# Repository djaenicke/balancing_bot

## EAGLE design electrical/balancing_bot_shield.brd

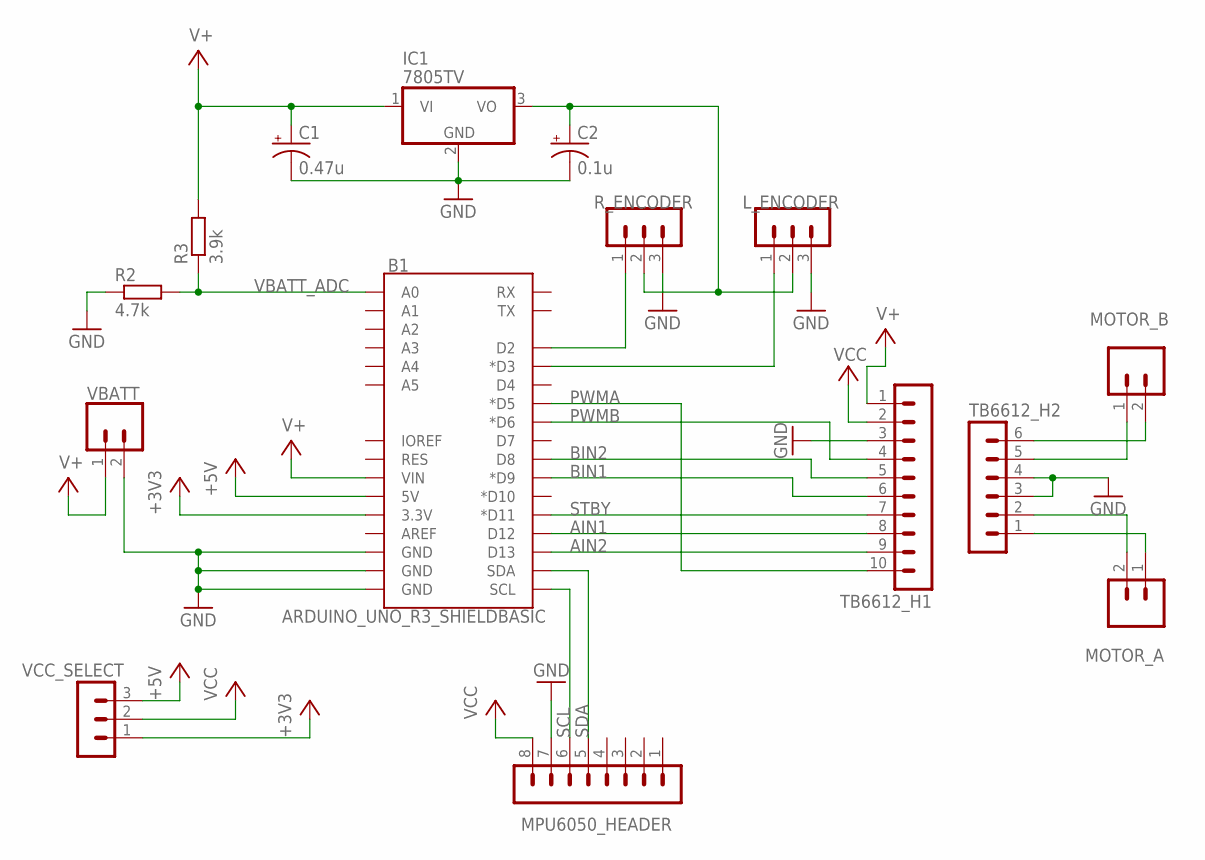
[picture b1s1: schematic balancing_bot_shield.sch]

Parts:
B1: ARDUINO_UNO_R3_SHIELDBASIC; UNO_R3_SHIELD
C1: 0.47u; E5-5
C2: 0.1u; E5-5
IC1: 7805TV; TO220V
L_ENCODER: MA03-1
MOTOR_A: CONN_025MM; SCREWTERMINAL-5MM-2
MOTOR_B: CONN_025MM; SCREWTERMINAL-5MM-2
MPU6050_HEADER: MA08-1
R2: 4.7k; 0207/10
R3: 3.9k; 0207/10
R_ENCODER: MA03-1
TB6612_H1: MA10-1
TB6612_H2: MA06-1
VBATT: CONN_025MM; SCREWTERMINAL-5MM-2
VCC_SELECT: MA03-1

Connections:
+3V3: B1.3.3V, VCC_SELECT.1
+5V: B1.5V, VCC_SELECT.3
AIN1: B1.D12, TB6612_H1.8
AIN2: B1.D13, TB6612_H1.9
BIN1: B1.D9 (*D9), TB6612_H1.6
BIN2: B1.D8, TB6612_H1.5
GND: B1.GND@0 (GND), B1.GND@1 (GND), B1.GND@2 (GND), C1.-, C2.-, IC1.2 (GND), L_ENCODER.3, MPU6050_HEADER.7, R2.1, R_ENCODER.3, TB6612_H1.3, TB6612_H2.3, TB6612_H2.4, VBATT.2
unnamed: B1.D2, R_ENCODER.1
unnamed: B1.D3 (*D3), L_ENCODER.1
unnamed: MOTOR_B.2, TB6612_H2.6
unnamed: MOTOR_B.1, TB6612_H2.5
unnamed: MOTOR_A.2, TB6612_H2.2
unnamed: MOTOR_A.1, TB6612_H2.1
unnamed: C2.+, IC1.3 (VO), L_ENCODER.2, R_ENCODER.2
PWMA: B1.D5 (*D5), TB6612_H1.10
PWMB: B1.D6 (*D6), TB6612_H1.4
SCL: B1.SCL, MPU6050_HEADER.6
SDA: B1.SDA, MPU6050_HEADER.5
STBY: B1.D11 (*D11), TB6612_H1.7
V+: B1.VIN, C1.+, IC1.1 (VI), R3.2, TB6612_H1.1, VBATT.1
VBATT_ADC: B1.A0, R2.2, R3.1
VCC: MPU6050_HEADER.8, TB6612_H1.2, VCC_SELECT.2

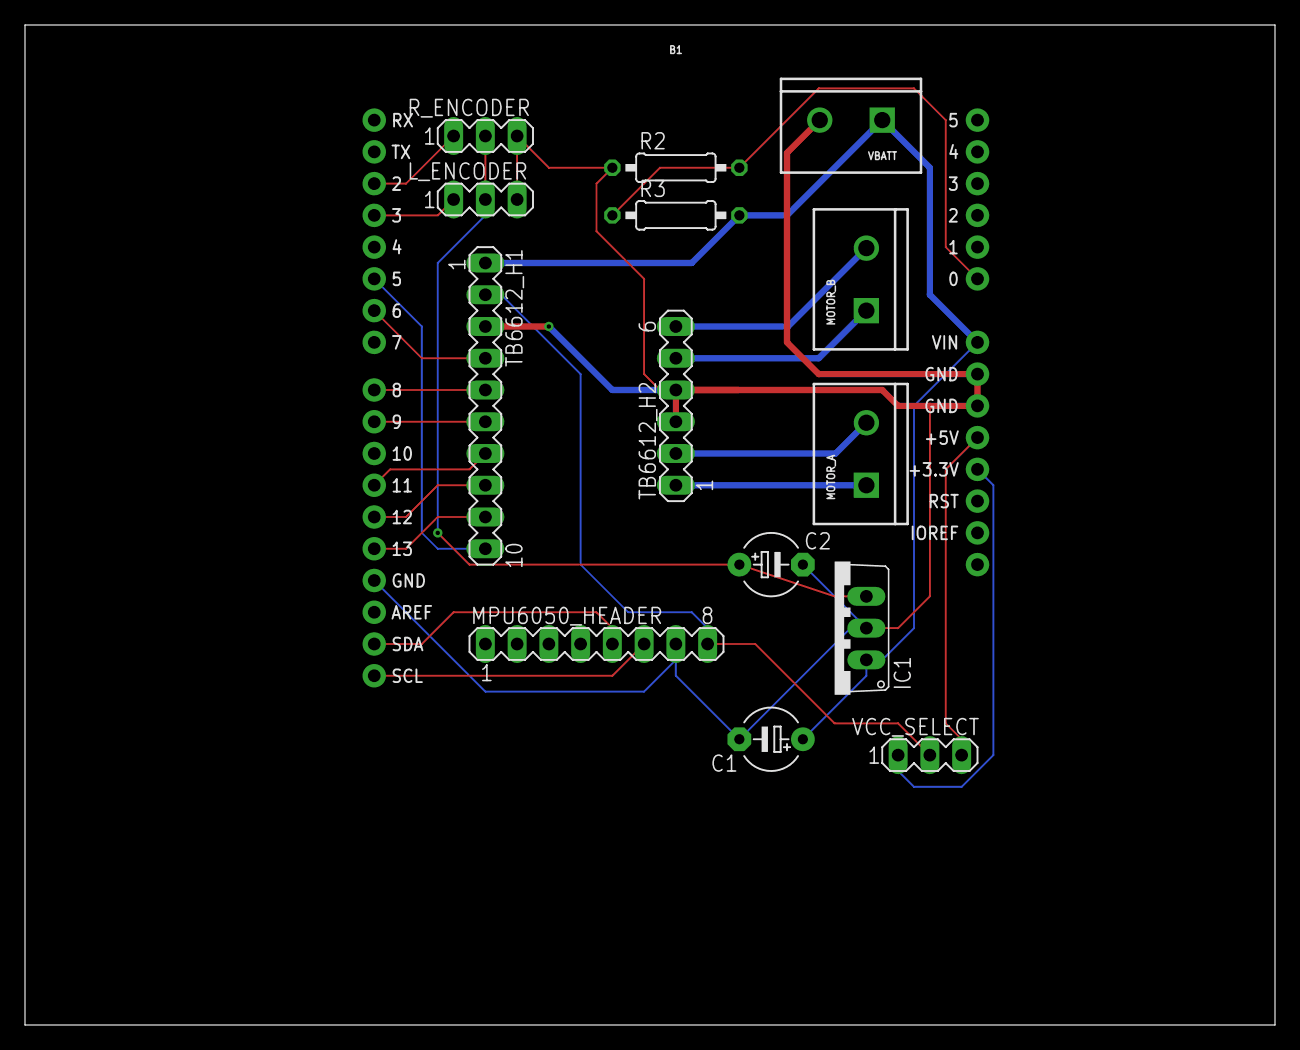
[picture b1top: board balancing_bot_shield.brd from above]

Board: 2 copper layers, 100.0 x 80.0 mm, 15 parts (0 on the bottom side), 22 nets.

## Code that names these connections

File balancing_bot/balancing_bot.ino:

#include <Adafruit_MPU6050.h>
#include <Adafruit_Sensor.h>
#include <SparkFun_TB6612.h>
#include <Wire.h>

#define DEBUG 0
#define LOG_FILTER_INPUTS 0
#define COMP_FILTER 1

Adafruit_MPU6050 mpu;
static volatile uint32_t sys_tick = 0;
static volatile uint32_t r_encoder_counts = 0;
static volatile uint32_t l_encoder_counts = 0;
static bool borked = false;   // Set true once we've toppled over, requries reset to clear

// Controller values
static const float dt = 0.005;
static const float MAX_PHI_FOR_CONTROL = 45.0f;
static const float KP_ANGLE = 45.0f;
static const float KI_ANGLE = 25.0f;
static const float KD_ANGLE = 0.0f;

#if COMP_FILTER
static const float alpha = 0.98;
static const float phi_dot_bias = 2.5f;
static float phi_deg = 0.0f;
static float phi_dot_dps = 0.0f;
#else
// Kalman filter start
static float phi_deg = 0.0f;        // State x(0)
static float phi_dot_bias = 2.5f;   // State x(1)
static float phi_dot_dps = 0.0f;
static const float Q_angle = 0.002;
static const float Q_bias = 0.05;
static const float R_angle =  0.5;
static const float dt_2 = dt * dt;
static float P_00 = 1e3;
static float P_01 = 0.0f;
static float P_10 = 0.0f;
static float P_11 = 1e3;;
static float K_0 = 0.0f;
static float K_1 = 0.0f;
// Kalman filter end
#endif

// Wheel encoders
static const uint8_t R_ENCODER_PIN = 2;
static const uint8_t L_ENCODER_PIN = 3;
static const uint16_t PULSES_PER_REV = 192;
static const uint16_t COUNTS_PER_REV = PULSES_PER_REV * 2;  // Triggered on rising and falling

// Motors
static const uint8_t MAX_PWM = 255;
static const uint8_t AIN1 = 12;
static const uint8_t BIN1 = 9;
static const uint8_t AIN2 = 13;
static const uint8_t BIN2 = 8;
static const uint8_t PWMA = 5;
static const uint8_t PWMB = 6;
static const uint8_t STBY = 10;
static const int8_t OFFSET_A = -1;  // either 1 or -1
static const int8_t OFFSET_B = -1;  // either 1 or -1
Motor r_motor = Motor(AIN1, AIN2, PWMA, OFFSET_A, STBY);
Motor l_motor = Motor(BIN1, BIN2, PWMB, OFFSET_B, STBY);

void initSysTicker(void);
uint32_t getSysTick(void);
void calculatePhi(void);
int16_t runAngleController(void);
void rightEncoderIsr(void);
void leftEncoderIsr(void);
uint32_t getRightEncoderCounts(void);
uint32_t getLeftEncoderCounts(void);
void clearEncoderCounts(void);
void initFailedloop(const String failure_msg);

void setup() {
  Serial.begin(115200);

  while (!Serial) {
    delay(10);
  }

  // Initialize the MPU6050
  if (!mpu.begin()) {
    initFailedloop("Failed to find MPU6050 chip");
  }

  mpu.setAccelerometerRange(MPU6050_RANGE_2_G);
  if (MPU6050_RANGE_2_G != mpu.getAccelerometerRange()) {
    initFailedloop("Failed to set MPU6050 accelerometer range");
  }

  mpu.setGyroRange(MPU6050_RANGE_500_DEG);
  if (MPU6050_RANGE_500_DEG != mpu.getGyroRange()) {
    initFailedloop("Failed to set MPU6050 gyro range");
  }

  mpu.setFilterBandwidth(MPU6050_BAND_260_HZ);
  if (MPU6050_BAND_260_HZ != mpu.getFilterBandwidth()) {
    initFailedloop("Failed to set MPU6050 filter bandwidth");
  }

  Serial.println("");
  delay(100);

  // Initialize the wheel encoder inputs
  pinMode(R_ENCODER_PIN, INPUT_PULLUP);
  pinMode(L_ENCODER_PIN, INPUT_PULLUP);
  attachInterrupt(digitalPinToInterrupt(R_ENCODER_PIN), rightEncoderIsr, CHANGE);
  attachInterrupt(digitalPinToInterrupt(L_ENCODER_PIN), leftEncoderIsr, CHANGE);

  // Initialize the system ticker
  initSysTicker();
}

void loop() {
  static uint32_t task_5ms_trigger_ticks = 2;  // Delay this task by 2ms
  static uint32_t task_100ms_trigger_ticks = 0;

  const uint32_t cur_sys_tick = getSysTick();

  if (cur_sys_tick > task_100ms_trigger_ticks) {
    task_100ms_trigger_ticks += 100;
#if DEBUG
    // Print the tilt angle in degrees
    Serial.print("phi = ");
    Serial.println(phi_deg);
  
    // Print the tilt angle rate in degrees / second
    Serial.print("phi_dot = ");
    Serial.println(phi_dot_dps);

    Serial.println("");
#endif
  }

  if (cur_sys_tick > task_5ms_trigger_ticks) {
    task_5ms_trigger_ticks += 5;

    // Sample and filter phi and phi_dot
    calculatePhi();

    const int16_t angle_pwm = runAngleController();
    const float phi_deg_abs = fabsf(phi_deg);
    if (phi_deg_abs < MAX_PHI_FOR_CONTROL && !borked) {
#if !LOG_FILTER_INPUTS && !DEBUG
      r_motor.drive(angle_pwm);
      l_motor.drive(angle_pwm);
#endif
    }
    else {
      r_motor.brake();
      l_motor.brake();
      borked = true;
    }
  }
}

void initSysTicker(void) {
  TCCR1A = 0;  // set entire TCCR0A register to 0
  TCCR1B = 0;  // same for TCCR0B
  TCNT1  = 0;  // initialize counter value to 0

  // Set compare match register for 1khz increments
  OCR1A = 249;  // = (16e6) / (1000 * 64) - 1 (must be < 256)

  // Turn on CTC mode
  TCCR1A |= (1 << WGM01);

  // Set CS01 and CS00 bits for 64 prescaler
  TCCR1B |= (1 << CS01) | (1 << CS00);

  // enable timer compare interrupt
  TIMSK1 |= (1 << OCIE0A);
}

ISR(TIMER1_COMPA_vect) {
  sys_tick++;
}

uint32_t getSysTick(void) {
  cli();  // disable interrupts
  const uint32_t temp = sys_tick;
  sei();  // enable interrupts
  return temp;
}

void calculatePhi(void)
{
  // Get new sensor events with the readings
  sensors_event_t a, g, temp;
  mpu.getEvent(&a, &g, &temp);
    
  // Radial rotation angle calculation formula; 
  // The negative sign indicates the direction.
  // Convert radians to degrees.
  const float phi_deg_m = -atan2f(a.acceleration.y , a.acceleration.z) * (180.0f / PI);
  const float phi_dot_dps_m = (-g.gyro.x * (180.0f / PI));

#if LOG_FILTER_INPUTS
  Serial.print(getSysTick());
  Serial.print(", ");
  Serial.print(phi_deg_m);
  Serial.print(", ");
  Serial.print(phi_dot_dps_m);
  Serial.println("");
#else
#if COMP_FILTER
  phi_dot_dps = phi_dot_dps_m - phi_dot_bias;
  const float gyro_angle = phi_dot_dps * dt;
  phi_deg = (alpha * (phi_deg + gyro_angle)) + ((1 - alpha) * phi_deg_m);
#else
  phi_deg += dt * (phi_dot_dps_m - phi_dot_bias);
  P_00 += (-dt * (P_10 + P_01)) + (P_11 * dt_2) + Q_angle;
  P_01 -= dt * P_11;
  P_10 -= dt * P_11;
  P_11 += Q_bias;

  const float y = phi_deg_m - phi_deg;
  const float S = P_00 + R_angle;
  K_0 = P_00 / S;
  K_1 = P_10 / S;

  phi_deg += K_0 * y;
  phi_dot_bias += K_1 * y;
  phi_dot_dps = phi_dot_dps_m - phi_dot_bias;
  P_00 -= K_0 * P_00;
  P_01 -= K_0 * P_01;
  P_10 -= K_1 * P_00;
  P_11 -= K_1 * P_01;
#endif
#endif
}

int16_t runAngleController(void)
{
  static float phi_deg_last = 0.0f;
  static float I = 0.0f;

  I += phi_deg;
  I = constrain(I, -300, 300);

  const int16_t u = (int16_t)constrain((KP_ANGLE * phi_deg) + (KI_ANGLE * I * dt) + (KD_ANGLE * ((phi_deg - phi_deg_last) / dt)), -MAX_PWM, MAX_PWM);
  phi_deg_last = phi_deg;
  return u;
}

void rightEncoderIsr(void)
{
  r_encoder_counts++;
}

void leftEncoderIsr(void)
{
  l_encoder_counts++;
}

uint32_t getRightEncoderCounts(void)
{
  cli();  // disable interrupts
  const uint32_t temp = r_encoder_counts;
  sei();  // enable interrupts
  return temp;
}

uint32_t getLeftEncoderCounts(void)
{
  cli();  // disable interrupts
  const uint32_t temp = l_encoder_counts;
  sei();  // enable interrupts
  return temp;
}

void clearEncoderCounts(void)
{
  cli();  // disable interrupts
  r_encoder_counts = 0;
  l_encoder_counts = 0;
  sei();  // enable interrupts
}

void initFailedloop(const String failure_msg) {
  Serial.println(failure_msg);
  while (1) {
    delay(10);
  }
}

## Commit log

2021-04-18 initial version
2021-04-19 redesigned the kalman filter for pitch angle
2021-04-25 working version using complementary filter
2021-04-25 added photos and cad files
2021-04-25 added system diagram
2021-04-25 added shield Eagle files

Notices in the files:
parts and their libraries:
SparkFun-Boards: Licensing: Creative Commons ShareAlike 4.0 International - https://creativecommons.org/licenses/by-sa/4.0
